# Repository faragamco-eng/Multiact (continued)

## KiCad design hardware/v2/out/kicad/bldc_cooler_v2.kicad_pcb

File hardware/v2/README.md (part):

# شماتیک و چیدمان درایو کولر — نسخه ۲ (برق شهر 220 VAC)

## فایل‌های آماده برای Altium / KiCad

| فایل | توضیح |
|---|---|
| [`out/kicad/`](out/kicad/) | **پروژه کامل KiCad 7**: شماتیک ۸ برگه (+ برگه اصلی)، برد با همه قطعات چیده‌شده، net class ها، قوانین DRC، کتابخانه محلی |
| [`out/bldc_cooler_v2_schematic.pdf`](out/bldc_cooler_v2_schematic.pdf) | شماتیک PDF (۹ صفحه) |
| [`out/bldc_cooler_v2_placement.pdf`](out/bldc_cooler_v2_placement.pdf) | چیدمان برد PDF |
| [`out/bldc_cooler_v2_altium_protel.net`](out/bldc_cooler_v2_altium_protel.net) | نت‌لیست فرمت Protel/Altium (راه جایگزین) |
| [`out/bom.csv`](out/bom.csv) | لیست قطعات (ستون Populate: `yes` یا `OPTION/DNP`) |

### باز کردن در Altium Designer

1. **روش اصلی:** `File → Import Wizard → KiCad Design Files` و انتخاب پوشه `out/kicad`
   (فایل‌های `.kicad_pro`، `.kicad_sch` و `.kicad_pcb`). خروجی: SchDoc برای هر برگه + PcbDoc با چیدمان.
   فرمت KiCad 7 است. Import Wizard در Altium Designer نسخه‌های جدید (22 به بعد) از KiCad 6/7 پشتیبانی می‌کند.
   **من Altium نداشتم و import را خودم تست نکرده‌ام.** پروژه با خود KiCad 7.0.11 بارگذاری و بررسی شده است.
2. **روش جایگزین:** یک PcbDoc خالی، سپس `Design → Import Changes` از روی `bldc_cooler_v2_altium_protel.net`.
   فوت‌پرینت‌ها با همان نام‌های کتابخانه KiCad هستند و باید در کتابخانه Altium شما وجود داشته باشند.

### بررسی‌هایی که روی همین فایل‌ها انجام شد (`./build.sh`)

| بررسی | نتیجه |
|---|---|
| سمبل‌ها، نام پین‌ها، پدهای footprint، عملکرد پین‌های MCU (کتابخانه KiCad 7.0.11 + داده ST) | **0 خطا** (289 قطعه، 199 نت) |
| KiCad نت‌لیست را **از روی شماتیک رسم‌شده** خروجی گرفت و با طراحی مقایسه شد | **0 اختلاف** (172 نت) |
| نت تک‌تک پدهای برد در برابر طراحی | **0 اختلاف** |
| DRC خود KiCad (فاصله‌ها، هم‌پوشانی، لبه برد، سوراخ‌ها) | **0 خطای مسدودکننده**؛ باقی‌مانده: 499 اتصال مسیرکشی‌نشده (مسیرکشی هنوز انجام نشده) و تداخل‌های ظاهری silkscreen |

### چیدمان برد (250 × 180 mm، دولایه)

| ناحیه | محتوا |
|---|---|
| چپ | ورودی AC: ترمینال، فیوز، وریستورها، GDT، چوک CM، خازن‌های X/Y، رله اصلی K1 و پیش‌شارژ K2 |
| وسط چپ | PFC: چوک 470 µH در بالا، کنترلر و قطعات کوچک؛ **دو خازن نو 470 µF/450 V موازی** در یک ردیف پایین‌تر؛ **محل ماژول باتری (DNP)** کنار باس |
| وسط راست | بالا: تغذیه کمکی (VIPer26، پیش‌رگولاتور) |
| پایین (بالای ردیف هیت‌سینک) | **اینورتر گسسته**: سه درایور IRS2186 در سوکت، هر کدام درست بالای دو MOSFET همان فاز، بوت‌استرپ، مقاومت‌های گیت، سه شنت، خازن‌های فیلم |
| راست بالا | **ناحیه SELV** پشت شیار فرز 2 mm (L شکل، زیر T1 و ISO7762): PHY پنل، رگولاتورهای باس پنل، **ترمینال پنل دوسیمه**، RS-485 (DNP) |
| راست پایین | MCU، رله‌های پمپ و تخلیه، ترمینال پمپ/تخلیه 220 V، ترمینال موتور |
| لبه پایین | **ردیف هیت‌سینک**: پل، MOSFET پیش‌رگولاتور، MOSFET PFC، دیود SiC و **شش MOSFET اینورتر TO-247** (عمودی، tab به سمت لبه، با پد عایق و پیچ M3 — قابل تعویض تکی) |

**قوانین برد (در پروژه):** net class `HV_mains` (59 نت برق شهر/باس): فاصله 1.5 mm، ترک 1.5 mm.
`Power_GND`: ترک 2 mm. فاصله داخلی پایه‌های درایورها/MOSFETها/VIPer/رله‌ها با قوانین مخصوص همان قطعه مجاز شده است.
**مرز SELV:** هیچ مسی در 4 mm اطراف شیار نباشد (به‌جز پدهای T1 و U7). خط و یادداشت آن روی لایه Dwgs.User است.

### گزینه‌ها و تجهیزات پایه

* **ماژول باتری (مرحله بعد):** U11 (RS-485)، J8، R99، JP1، C60، F4، J9 روی برد جا دارند ولی **مونتاژ نمی‌شوند** (DNP).
  برای نسخه باتری فقط همین‌ها نصب می‌شوند.
* **پنل:** ترمینال دوسیمه J7 (SELV) و مدار باس پنل کامل روی برد است. طراحی خود پنل در مرحله بعد.
* **تجهیزات پایه از حالا:** 4 سوراخ M3 بدون آبکاری (بدون مسیر خزشی)، 3 فیدوشیال برای مونتاژ ماشینی، 10 نقطه تست
  (+15V، +3V3، GND، درایو گیت PFC، جریان فاز U، UART، +3V3S، GND_S، باس پنل)، کانکتور SWD سمت داغ و سمت SELV،
  LED ولتاژ بالا و LED وضعیت در هر دو سمت.

### کار باقی‌مانده روی برد (دستی)

مسیرکشی انجام نشده است. ترتیب پیشنهادی:
1. حلقه‌های پرجریان: PFC (پل → چوک → MOSFET → دیود → خازن‌ها → شنت → پل) کوتاه و پهن.
2. هر فاز: درین MOSFET بالا ← خازن فیلم همان فاز (C35/C40/C36) ← شنت، حلقه کوچک. درایور با مسیر گیت و برگشت کوتاه (VS مستقیم به سورس MOSFET بالا).
3. شنت‌ها با اتصال Kelvin و ستاره زمین (NT1).
4. سپس سیگنال‌ها. آخر کار polygon زمین در دو سمت (جدا: `GND/PGND` و `GND_S`).

---

## جزئیات طراحی مدار (نسخه ۲)

> نسخه ۱ (`hardware/netlist.md`) برای six-step و تک‌شنت بود و **جایگزین شده است**.

## چطور ساخته و بررسی شده

شماتیک به‌صورت **کد** در [`schematic.py`](schematic.py) تعریف شده است (هر قطعه، هر پین، هر نت). اسکریپت
[`check_and_build.py`](check_and_build.py) آن را با منابع رسمی مقایسه می‌کند و خروجی‌ها را می‌سازد:

| بررسی | منبع |
|---|---|
| هر سمبل وجود دارد، شماره و **نام** هر پین درست است (زنجیره extends حل می‌شود) | کتابخانه رسمی KiCad symbols |
| هر footprint وجود دارد و هر پین وصل‌شده **پد واقعی** دارد | کتابخانه رسمی KiCad footprints |
| پین‌های STM32G431 و STM32C011 با شماره پایه ST یکی است و **هر عملکرد لازم (TIM1، OPAMP، USART، ADC، COMP) واقعاً روی آن پین وجود دارد** | ST `STM32_open_pin_data` |
| نت تک‌اتصالی، تایپوی نت تغذیه، **هیچ قطعه‌ای جز ایزولاتور و ترانس SELV را به سمت برق شهر وصل نکند** | قوانین داخلی |

نتیجه فعلی: **289 قطعه، 199 نت، 0 خطا** (KiCad 7.0.11). سه هشدار باقی‌مانده عمدی هستند: ترانس سفارشی،
پدهای خالی 9/10 ترانس و پین NC رگولاتور. بررسی‌کننده با ۴ خطای عمدی آزمایش شد و هر ۴ را گرفت.

خروجی‌ها در [`out/`](out/):

* `netlist.md` — جدول برگه‌به‌برگه + فهرست نت‌ها
* `bom.csv` — لیست قطعات گروه‌بندی‌شده
* `bldc_cooler_v2.net` — **نت‌لیست KiCad**: در PCB Editor از مسیر *File → Import → Netlist* وارد کنید تا همه
  footprintها و اتصالات (ratsnest) بیایند
* `check_report.txt` — گزارش بررسی
* `calc_v2.md` — محاسبات (PFC، فلای‌بک، سنجش جریان، باس پنل)

اجرای مجدد (کتابخانه‌ها یک بار clone شوند):

```bash
git clone --depth 1 https://gitlab.com/kicad/libraries/kicad-symbols.git
git clone --depth 1 --filter=blob:none --no-checkout https://gitlab.com/kicad/libraries/kicad-footprints.git
git clone --depth 1 --filter=blob:none --sparse https://github.com/STMicroelectronics/STM32_open_pin_data.git
(cd STM32_open_pin_data && git sparse-checkout set --no-cone '/mcu/STM32G431C(6-8-B)Tx.xml' '/mcu/STM32C011F(4-6)Px.xml')
python3 hardware/v2/check_and_build.py --symbols kicad-symbols --footprints kicad-footprints --pindata STM32_open_pin_data
python3 hardware/v2/calc_v2.py
```

## برگه‌ها

| برگه | محتوا | نکات کلیدی |
|---|---|---|
| ۱ ورودی AC | فیوز 10 A، سه MOV نوع **S14K385** + GDT به ارت، X/Y و چوک CM، **K1 رله اصلی** و **K2 پیش‌شارژ با PTC**، یکسوساز تغذیه کمکی **قبل از رله‌ها**، سنجش خط و نول (1:301) | باس فقط وقتی ولتاژ ورودی در محدوده است وصل می‌شود؛ در OV رله‌ها در یک نیم‌سیکل باز می‌شوند |
| ۲ PFC | پل GBU1010، چوک 470 µH، MOSFET 650 V، دیود SiC، شنت 25 mΩ، **NCP1653**، **2×470 µF/450 V نو، 105 °C، موازی** (940 µF: نگه‌داری 49 ms، ریپل 10 V p-p)، بلیدر 3×100k + LED ولتاژ بالا (390 V ⇐ 60 V در ~9 دقیقه) | MCU با Q2 می‌تواند PFC را خاموش کند |
| ۳ تغذیه کمکی | **دیود D29 از باس DC** (نگه‌داری حدود 4 s بعد از قطع برق، کار در حالت باتری) + **پیش‌رگولاتور MOSFET 1500 V** (ورودی فلای‌بک ≤ 395 V حتی در 440 VAC)، VIPer26LN، ترانس EF20 با سه سیم‌پیچ (15 V داغ، 5.5 V و 31 V ایزوله)، باک AP63203 برای 3.3 V داغ، LDO برای 3.3 V ایزوله | پایداری حتی وقتی موتور و PFC قطع‌اند ⇒ پنل همیشه کار می‌کند و آلارم نشان می‌دهد |
| ۴ اینورتر | **گسسته و قابل تعمیر:** 3× **IRS2186** (DIP-8 در سوکت) + 6× **STW24N60DM2** (TO-247، 600 V، دیود بدنه سریع؛ جایگزین IGBT STGW20H60DF)، بوت‌استرپ UF4007 + 10 Ω + 4.7 µF، گیت 10 Ω / 10k، **سه شنت 25 mΩ** در سورس‌های پایین، NTC و **ترموسوئیچ NC 90 °C** هیت‌سینک (به BKIN)، سنجش باس 1:150، NetTie ستاره زمین | ورودی‌ها **فعال-بالا** با pull-down ⇒ `IPM_LIN_ACTIVE_LOW=0`. IRS2186 زمان مرده ندارد ⇒ dead time از TIM1 (≥ 1 µs). اتصال کوتاه: OPAMP → COMP1/2/4 → BKIN2 (داخلی) |
| ۵ MCU | STM32G431CBT6: TIM1 شش PWM، OPAMP1/2/3 و COMP1/2/4 برای سه فاز، ADC برای باس/خط/نول/دما، USART1 به ایزولاتور، ۴ رله، SWD | همه عملکردها با داده ST تأیید شد |
| ۶ رله‌ها | K3 **پمپ** و K4 **تخلیه** (220 VAC)، فیوز 2 A، درایور MOSFET + دیود هرزگرد، اسنابر RC اختیاری | پمپ و تخلیه از **بعد از K1** تغذیه می‌شوند ⇒ در اضافه‌ولتاژ هم قطع می‌شوند |
| ۷ سمت ایزوله | **ISO7762DW (ایزولاسیون تقویت‌شده، SOIC-16 پهن)**، **STM32C011** برای باس پنل و RS-485، باس پنل دوسیمه (LM317 محدودکننده جریان 150 mA + LM317 تنظیم 24/16 V، سنجش جریان برگشتی)، SP3485 به ماژول باتری (DNP) | باس پنل SELV است و پلاریته در پنل مهم نیست |
| ۸ گزینه باتری (DNP) + مکانیک | فیوز DC 5 A / 500 V، ترمینال باس، سوراخ‌ها، فیدوشیال، نقاط تست | در نسخه برق شهر مونتاژ نمی‌شود |

## تفاوت‌ها با اسناد قبلی (مهم)

1. **طبقه قدرت گسسته به جای IPM** (به درخواست شما برای تعمیرپذیری): هر MOSFET و هر درایور جداگانه تعویض می‌شود.
   **IRF840 مناسب نیست** (جدول «Inverter switch losses» در `out/calc_v2.md`: حدود 145 W تلفات در برابر 23 W،
   به‌خاطر 0.85 Ω و دیود بدنه کند 460 ns؛ و 500 V فقط 1.28 برابر باس 390 V است). خازن‌های قدیمی
   1200 µF/200 V بررسی شدند (سه‌تا سری قابل استفاده بود) ولی **به انتخاب شما خازن نو 2×470 µF/450 V** گذاشته شد:
   بدون مقاومت تعادل، بدون ریسک نشتی خازن کهنه، نگه‌داری 49 ms به جای 21 ms. حالت سه‌تا سری در فریمور به‌صورت
   گزینه (`cap_tol`) باقی است.
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
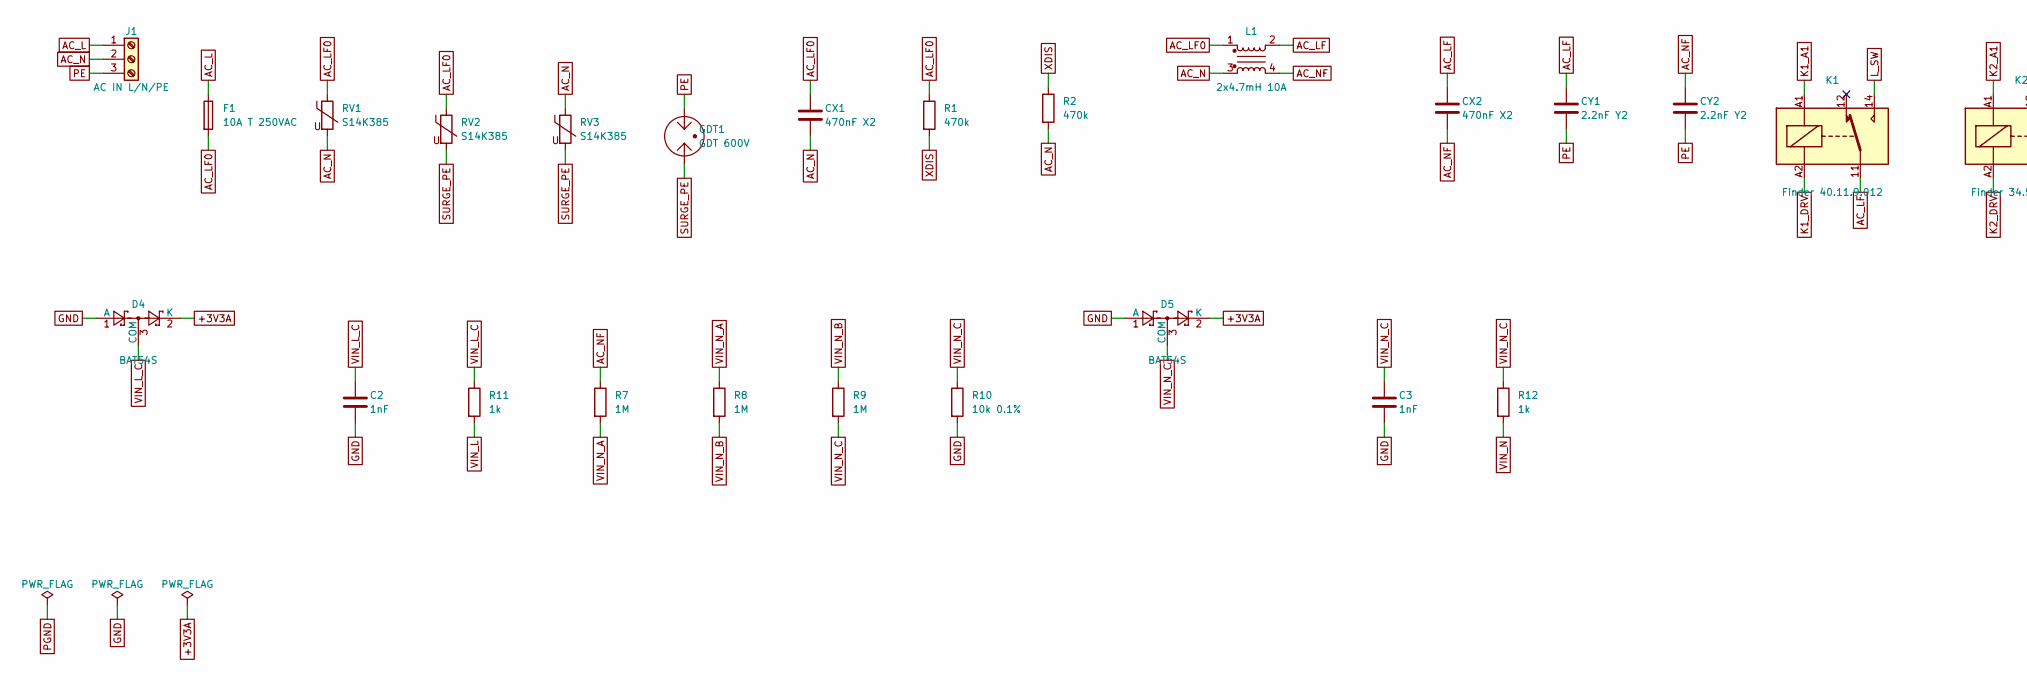
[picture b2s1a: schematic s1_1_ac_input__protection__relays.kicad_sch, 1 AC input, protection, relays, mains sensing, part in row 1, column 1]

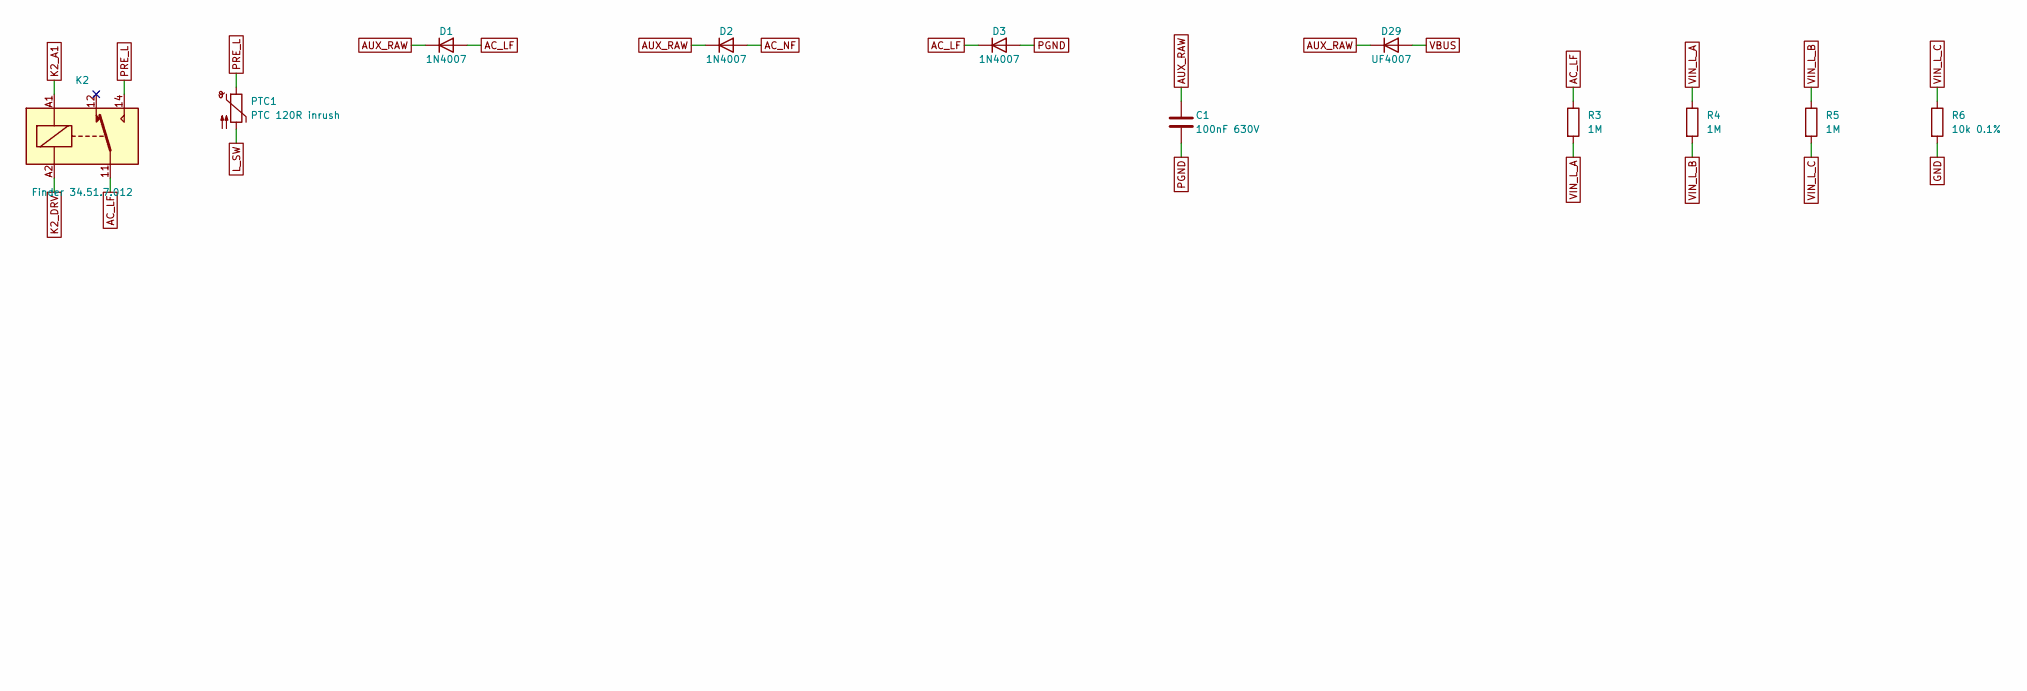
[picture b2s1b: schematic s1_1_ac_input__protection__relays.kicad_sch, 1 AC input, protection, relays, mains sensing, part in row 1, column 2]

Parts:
C1: 100nF 630V; C_Rect_L18.0mm_W6.0mm_P15.00mm_FKS3_FKP3
C2, C3: 1nF; C_0603_1608Metric
CX1: 470nF X2; C_Rect_L18.0mm_W7.0mm_P15.00mm_FKS3_FKP3; MPN X2 310VAC
CX2: 470nF X2; C_Rect_L18.0mm_W7.0mm_P15.00mm_FKS3_FKP3
CY1, CY2: 2.2nF Y2; C_Disc_D11.0mm_W5.0mm_P7.50mm; MPN Y2 300VAC
D1, D2, D3: 1N4007; D_DO-41_SOD81_P10.16mm_Horizontal; MPN 1N4007
D4, D5: BAT54S; SOT-23; MPN BAT54S
D29: UF4007; D_DO-41_SOD81_P10.16mm_Horizontal; MPN UF4007 (1000 V)
F1: 10A T 250VAC; Fuseholder_Cylinder-5x20mm_Bulgin_FX0457_Horizontal_Closed; MPN 5x20 ceramic 10 A time-lag
GDT1: GDT 600V; GDT_Axial_P15.24mm; MPN axial 2-electrode GDT 600 V (e.g. Bourn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
J1: AC IN L/N/PE; TerminalBlock_Phoenix_MKDS-1,5-3-5.08_1x03_P5.08mm_Horizont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; MPN Phoenix MKDS 1,5/3-5,08
K1: Finder 40.11.9.012; Relay_SPDT_Finder_40.11; MPN Finder 40.11.9.012.0000 (10 A, 12 V coi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
K2: Finder 34.51.7.012; Relay_SPDT_Finder_34.51_Vertical; MPN Finder 34.51.7.012.0010
L1: 2x4.7mH 10A; CMC_Toroid_4P_25x15mm; MPN toroidal CM choke 2 x 4.7 mH, >= 10 A (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
PTC1: PTC 120R inrush; C_Disc_D11.0mm_W5.0mm_P7.50mm; MPN inrush PTC rated >= 80 J at 265 VAC (94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
R1, R2: 470k; R_1206_3216Metric
R3, R4, R5, R7, R8, R9: 1M; R_1206_3216Metric
R6, R10: 10k 0.1%; R_0603_1608Metric
R11, R12: 1k; R_0603_1608Metric
RV1: S14K385; RV_Disc_D15.5mm_W11mm_P7.5mm; MPN EPCOS S14K385
RV2, RV3: S14K385; RV_Disc_D15.5mm_W11mm_P7.5mm

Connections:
+3V3A: D4.2 (K), D5.2 (K); also elsewhere on the board
AC_L: F1.1, J1.1
AC_LF: CX2.1, CY1.1, D1.2 (A), D3.1 (K), K1.11, K2.11, L1.2, R3.1
AC_LF0: CX1.1, F1.2, L1.1, R1.1, RV1.1, RV2.1
AC_N: CX1.2, J1.2, L1.3, R2.2, RV1.2, RV3.1
AC_NF: CX2.2, CY2.1, D2.2 (A), L1.4, R7.1; also elsewhere on the board
AUX_RAW: C1.1, D1.1 (K), D2.1 (K), D29.1 (K); also elsewhere on the board
GND: C2.2, C3.2, D4.1 (A), D5.1 (A), R6.2, R10.2; also elsewhere on the board
K1_A1: K1.A1; also elsewhere on the board
K1_DRV: K1.A2; also elsewhere on the board
K2_A1: K2.A1; also elsewhere on the board
K2_DRV: K2.A2; also elsewhere on the board
L_SW: K1.14, PTC1.2; also elsewhere on the board
PE: CY1.2, CY2.2, GDT1.3, J1.3; also elsewhere on the board
PGND: C1.2, D3.2 (A); also elsewhere on the board
PRE_L: K2.14, PTC1.1
SURGE_PE: GDT1.1, RV2.2, RV3.2
VBUS: D29.2 (A); also elsewhere on the board
VIN_L: R11.2; also elsewhere on the board
VIN_L_A: R3.2, R4.1
VIN_L_B: R4.2, R5.1
VIN_L_C: C2.1, D4.3 (COM), R5.2, R6.1, R11.1
VIN_N: R12.2; also elsewhere on the board
VIN_N_A: R7.2, R8.1
VIN_N_B: R8.2, R9.1
VIN_N_C: C3.1, D5.3 (COM), R9.2, R10.1, R12.1
XDIS: R1.2, R2.1

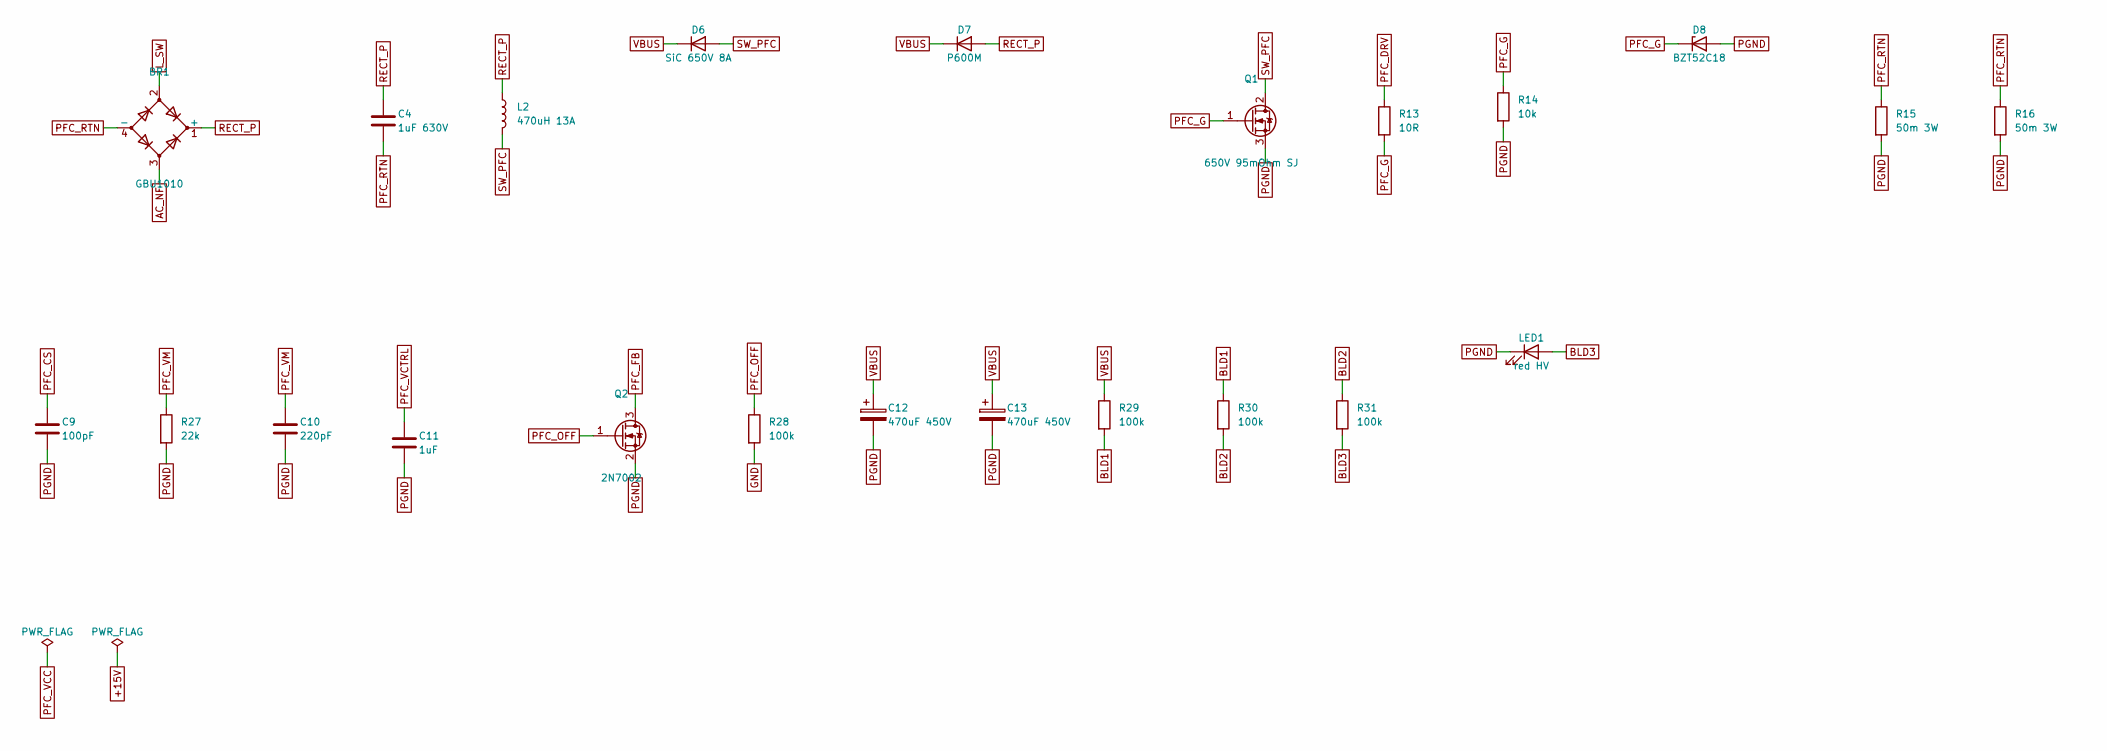
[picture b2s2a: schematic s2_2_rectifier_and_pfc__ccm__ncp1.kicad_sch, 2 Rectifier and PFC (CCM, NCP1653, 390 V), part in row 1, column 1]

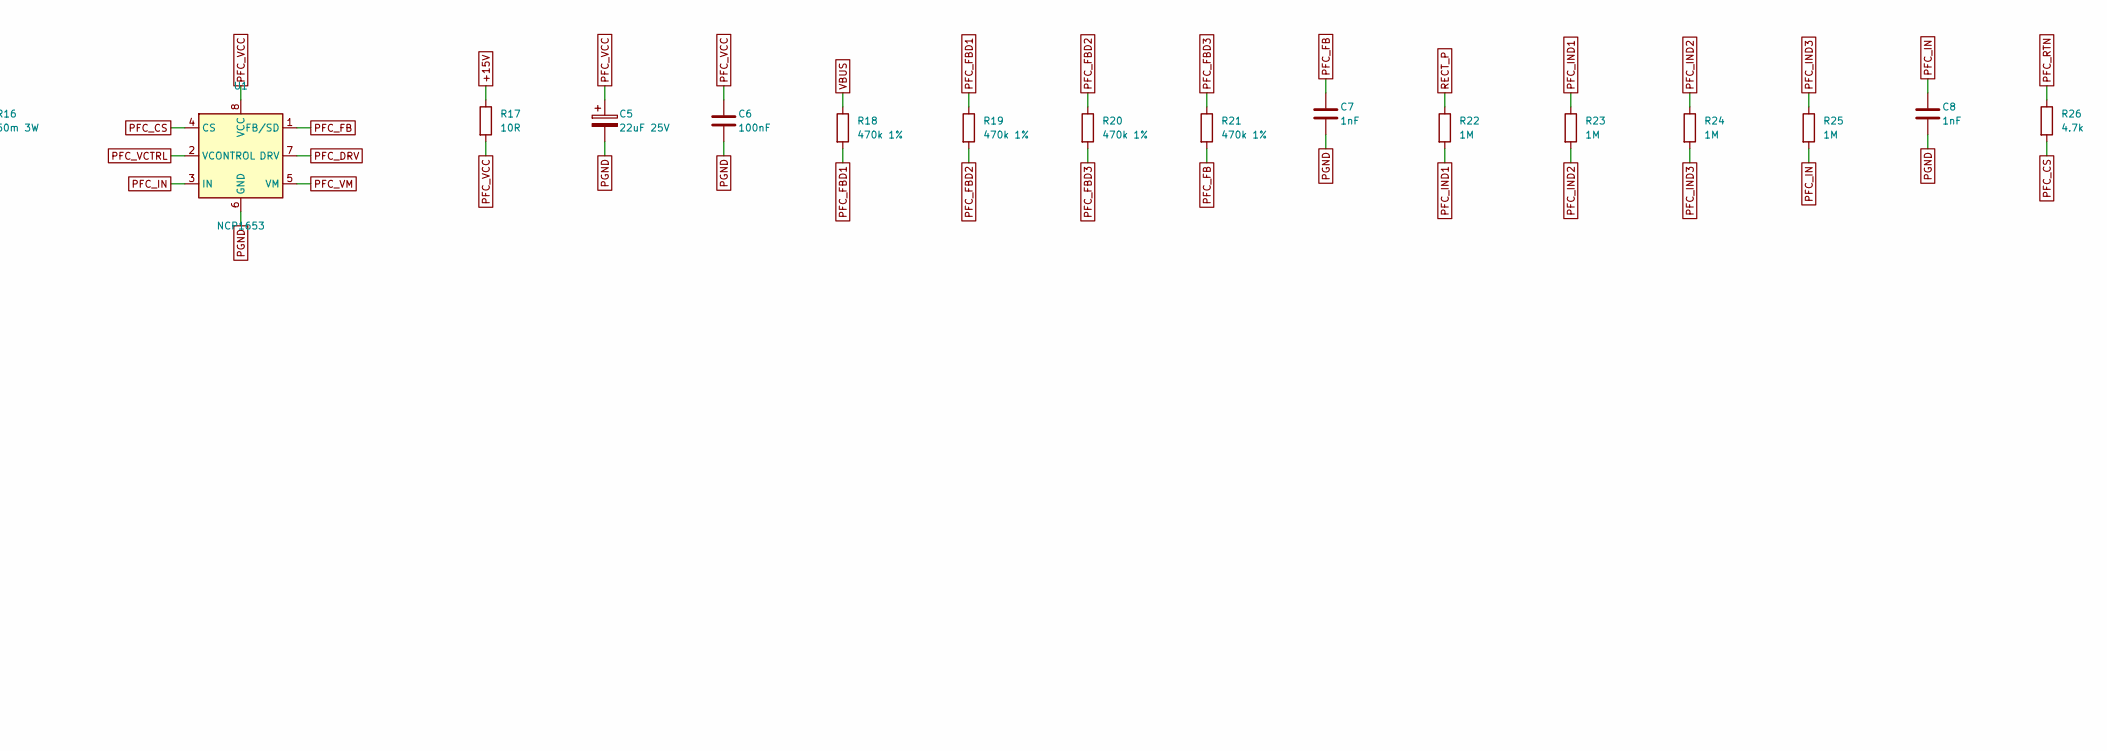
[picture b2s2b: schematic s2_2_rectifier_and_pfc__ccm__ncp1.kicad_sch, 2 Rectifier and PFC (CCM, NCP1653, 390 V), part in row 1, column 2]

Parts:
BR1: GBU1010; Diode_Bridge_Vishay_GBU; MPN GBU1010 (10 A 1000 V) on heatsink
C4: 1uF 630V; C_Rect_L26.5mm_W8.5mm_P22.50mm_MKS4
C5: 22uF 25V; CP_Radial_D8.0mm_P3.50mm
C6: 100nF; C_0603_1608Metric
C7, C8: 1nF; C_0603_1608Metric
C9: 100pF; C_0603_1608Metric
C10: 220pF; C_0603_1608Metric
C11: 1uF; C_0805_2012Metric
C12, C13: 470uF 450V; CP_Radial_D35.0mm_P10.00mm_SnapIn; MPN 470 uF 450 V 105 C >= 5000 h snap-in D3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
D6: SiC 650V 8A; TO-220-2_Vertical; MPN Wolfspeed C3D08065A / Infineon IDH08G65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
D7: P600M; D_DO-201AD_P15.24mm_Horizontal; MPN P600M / 1N5408 inrush bypass
D8: BZT52C18; D_SOD-123; MPN BZT52C18
L2: 470uH 13A; L_Toroid_Vertical_L46.0mm_W19.1mm_P21.80mm_Bourns_5700; MPN toroid ~46 mm OD (e.g. Kool Mu 0077083A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
LED1: red HV; LED_0805_2012Metric; MPN high-efficiency red, 'HIGH VOLTAGE'
Q1: 650V 95mOhm SJ; TO-247-3_Vertical; MPN Infineon IPW65R095C7 / ST STW40N60M6 (h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
Q2: 2N7002; SOT-23; MPN 2N7002
R13, R17: 10R; R_0603_1608Metric
R14: 10k; R_0603_1608Metric
R15, R16: 50m 3W; R_2512_6332Metric
R18, R19, R20, R21: 470k 1%; R_1206_3216Metric
R22, R23, R24, R25: 1M; R_1206_3216Metric
R26: 4.7k; R_0603_1608Metric
R27: 22k; R_0603_1608Metric
R28: 100k; R_0603_1608Metric
R29, R30, R31: 100k; R_1206_3216Metric
U1: NCP1653; SOIC-8_3.9x4.9mm_P1.27mm; MPN onsemi NCP1653ADR2G (67 kHz)

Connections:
+15V: R17.1; also elsewhere on the board
AC_NF: BR1.3; also elsewhere on the board
BLD1: R29.2, R30.1
BLD2: R30.2, R31.1
BLD3: LED1.2 (A), R31.2
GND: R28.2; also elsewhere on the board
L_SW: BR1.2; also elsewhere on the board
PFC_CS: C9.1, R26.2, U1.4 (CS)
PFC_DRV: R13.1, U1.7 (DRV); also elsewhere on the board
PFC_FB: C7.1, Q2.3 (D), R21.2, U1.1 (FB/SD)
PFC_FBD1: R18.2, R19.1
PFC_FBD2: R19.2, R20.1
PFC_FBD3: R20.2, R21.1
PFC_G: D8.1 (K), Q1.1 (G), R13.2, R14.1
PFC_IN: C8.1, R25.2, U1.3 (IN)
PFC_IND1: R22.2, R23.1
PFC_IND2: R23.2, R24.1
PFC_IND3: R24.2, R25.1
PFC_OFF: Q2.1 (G), R28.1; also elsewhere on the board
PFC_RTN: BR1.4 (-), C4.2, R15.1, R16.1, R26.1
PFC_VCC: C5.1, C6.1, R17.2, U1.8 (VCC)
PFC_VCTRL: C11.1, U1.2 (VCONTROL)
PFC_VM: C10.1, R27.1, U1.5 (VM)
PGND: C5.2, C6.2, C7.2, C8.2, C9.2, C10.2, C11.2, C12.2, C13.2, D8.2 (A), LED1.1 (K), Q1.3 (S), Q2.2 (S), R14.2, R15.2, R16.2, R27.2, U1.6 (GND); also elsewhere on the board
RECT_P: BR1.1 (+), C4.1, D7.2 (A), L2.1, R22.1
SW_PFC: D6.2 (A), L2.2, Q1.2 (D)
VBUS: C12.1, C13.1, D6.1 (K), D7.1 (K), R18.1, R29.1; also elsewhere on the board

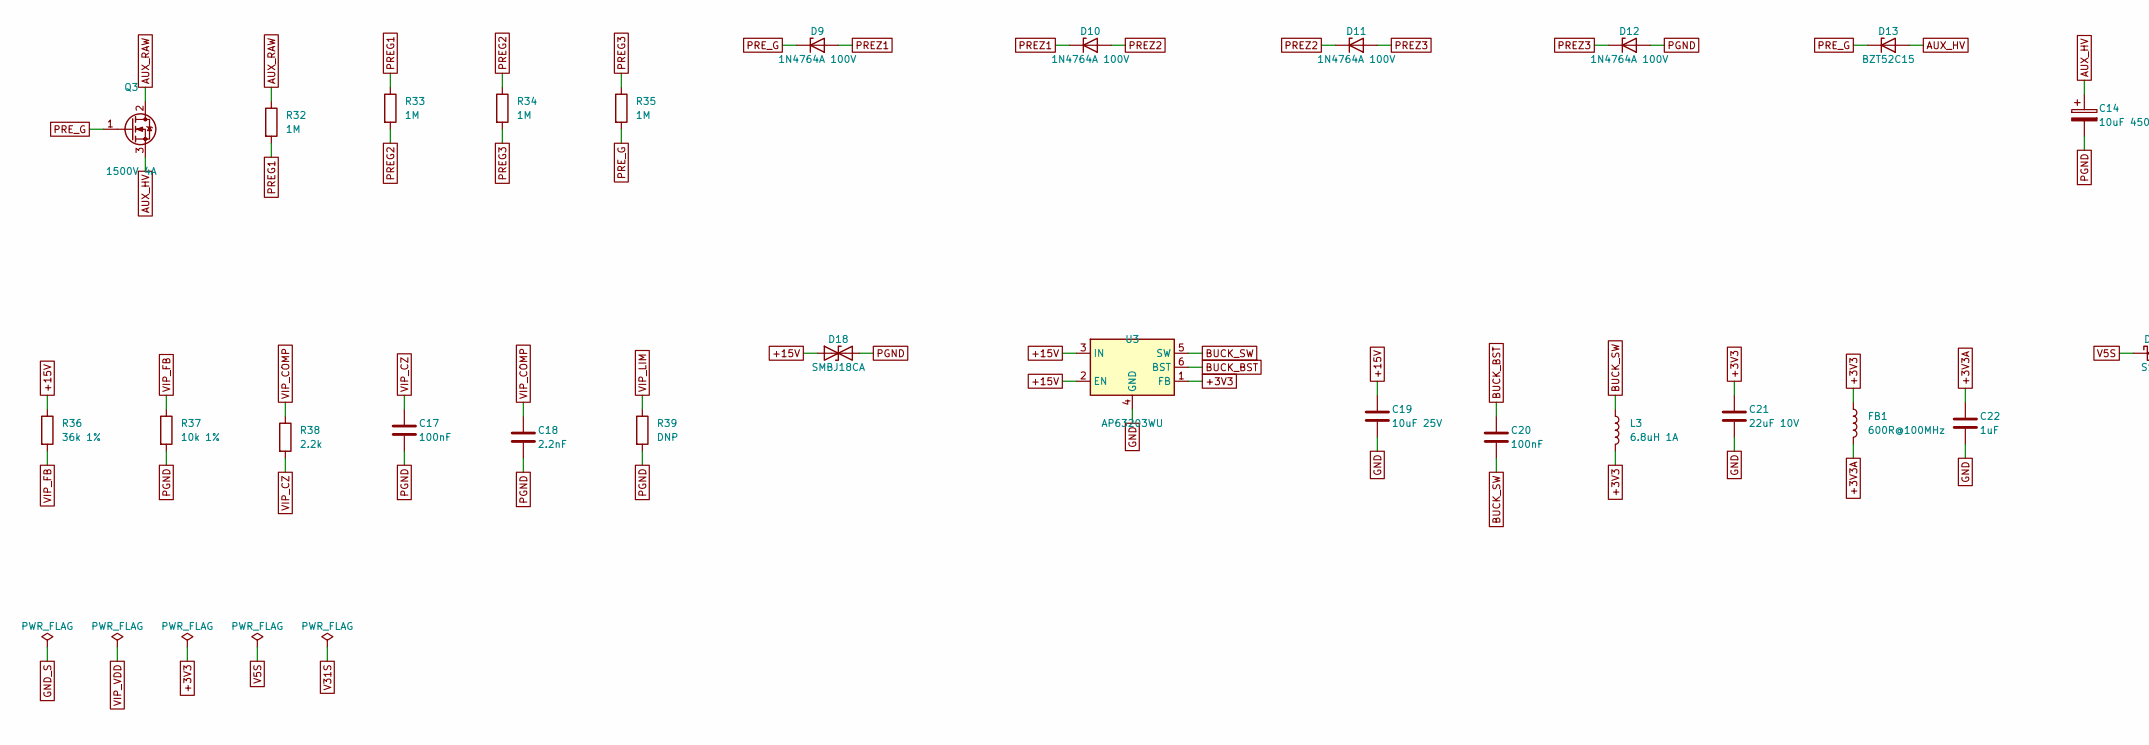
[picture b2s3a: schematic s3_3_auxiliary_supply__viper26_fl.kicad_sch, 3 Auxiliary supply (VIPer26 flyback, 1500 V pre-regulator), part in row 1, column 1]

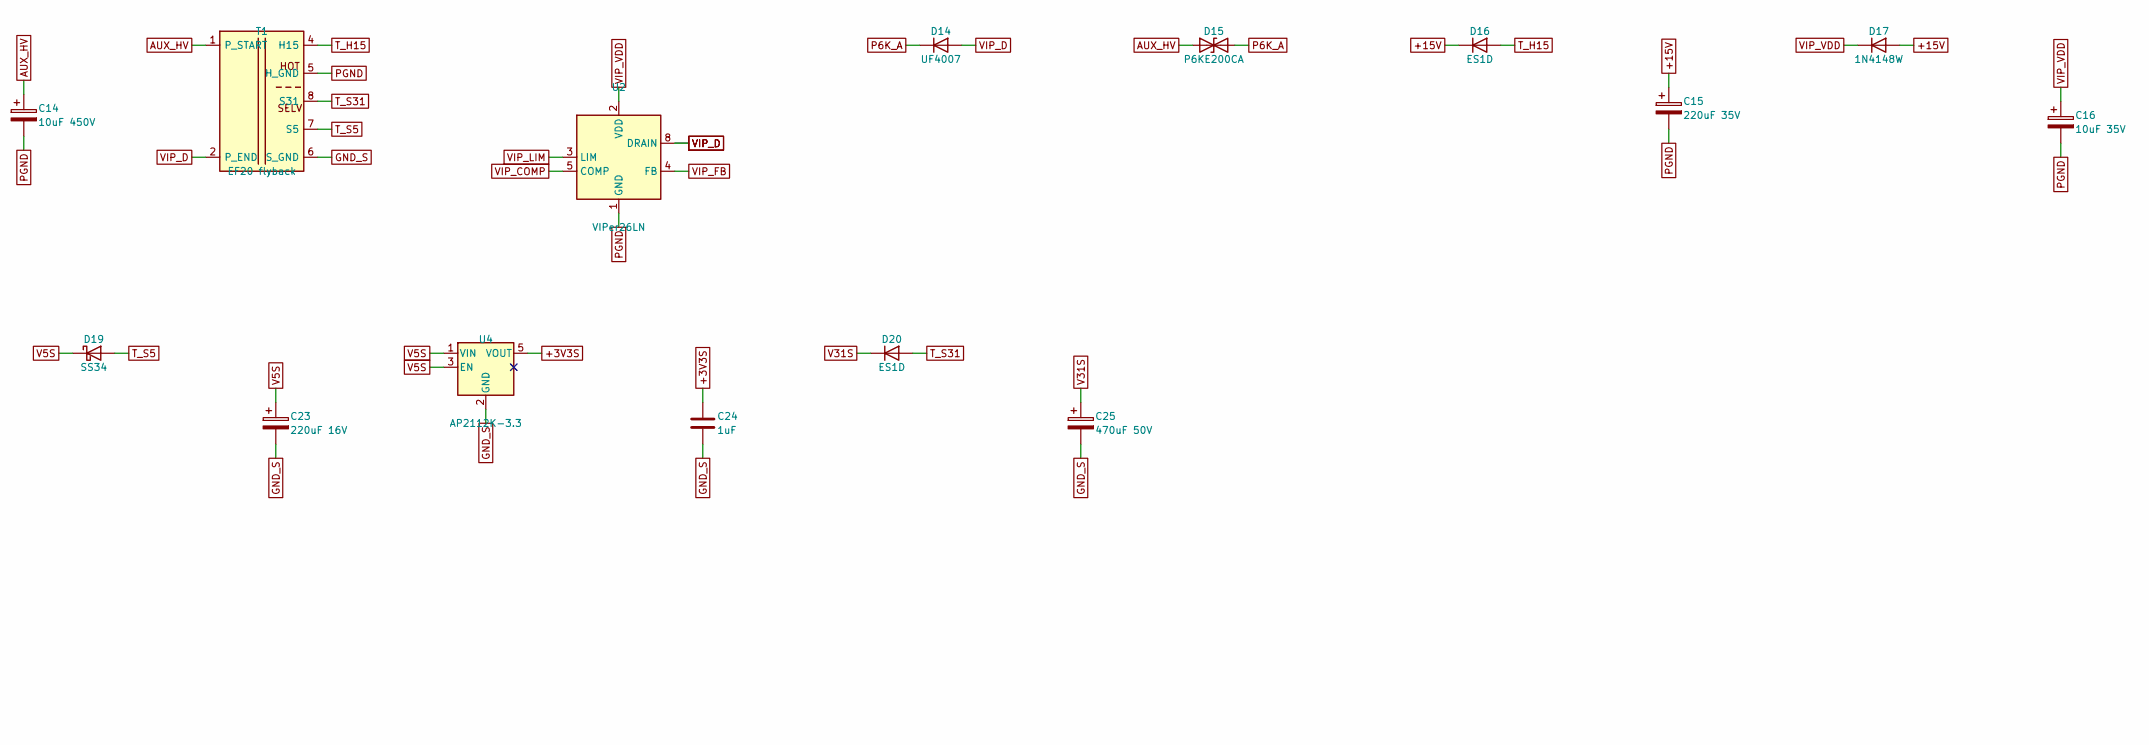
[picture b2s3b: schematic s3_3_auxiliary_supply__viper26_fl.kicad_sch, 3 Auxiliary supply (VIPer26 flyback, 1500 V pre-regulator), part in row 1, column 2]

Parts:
C14: 10uF 450V; CP_Radial_D10.0mm_P5.00mm
C15: 220uF 35V; CP_Radial_D8.0mm_P3.50mm
C16: 10uF 35V; CP_Radial_D8.0mm_P3.50mm
C17, C20: 100nF; C_0603_1608Metric
C18: 2.2nF; C_0603_1608Metric
C19: 10uF 25V; C_1206_3216Metric
C21: 22uF 10V; C_1206_3216Metric
C22, C24: 1uF; C_0603_1608Metric
C23: 220uF 16V; CP_Radial_D8.0mm_P3.50mm
C25: 470uF 50V; CP_Radial_D10.0mm_P5.00mm
D9, D10, D11, D12: 1N4764A 100V; D_DO-41_SOD81_P10.16mm_Horizontal; MPN 1N4764A
D13: BZT52C15; D_SOD-123; MPN BZT52C15
D14: UF4007; D_DO-41_SOD81_P10.16mm_Horizontal; MPN UF4007
D15: P6KE200CA; D_DO-41_SOD81_P10.16mm_Horizontal; MPN P6KE200CA (bidirectional, 200 V clamp)
D16, D20: ES1D; D_SMA; MPN ES1D
D17: 1N4148W; D_SOD-123; MPN 1N4148W
D18: SMBJ18CA; D_SMB; MPN SMBJ18CA
D19: SS34; D_SMA; MPN SS34
FB1: 600R@100MHz; L_0603_1608Metric; MPN ferrite bead
L3: 6.8uH 1A; L_Bourns_SRN6045TA; MPN Bourns SRN6045TA-6R8M
Q3: 1500V 4A; TO-247-3_Vertical; MPN ST STW4N150 (on main heatsink, insulate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
R32, R33, R34, R35: 1M; R_1206_3216Metric
R36: 36k 1%; R_0603_1608Metric
R37: 10k 1%; R_0603_1608Metric
R38: 2.2k; R_0603_1608Metric
R39: DNP; R_0603_1608Metric
T1: EF20 flyback; Transformer_Myrra_EF20_7408x; MPN custom, see calc/transformer spec
U2: VIPer26LN; DIP-8-N6_W7.62mm; MPN ST VIPer26LN (60 kHz)
U3: AP63203WU; TSOT-23-6; MPN Diodes AP63203WU (fixed 3.3 V)
U4: AP2112K-3.3; SOT-23-5; MPN Diodes AP2112K-3.3TRG1

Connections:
+3V3: C21.1, FB1.1, L3.2, U3.1 (FB); also elsewhere on the board
+3V3A: C22.1, FB1.2; also elsewhere on the board
+3V3S: C24.1, U4.5 (VOUT); also elsewhere on the board
+15V: C15.1, C19.1, D16.1 (K), D17.2 (A), D18.1 (A1), R36.1, U3.2 (EN), U3.3 (IN); also elsewhere on the board
AUX_HV: C14.1, D13.2 (A), D15.1 (A1), Q3.3 (S), T1.1 (P_START)
AUX_RAW: Q3.2 (D), R32.1; also elsewhere on the board
BUCK_BST: C20.1, U3.6 (BST)
BUCK_SW: C20.2, L3.1, U3.5 (SW)
GND: C19.2, C21.2, C22.2, U3.4 (GND); also elsewhere on the board
GND_S: C23.2, C24.2, C25.2, T1.6 (S_GND), U4.2 (GND); also elsewhere on the board
P6K_A: D14.1 (K), D15.2 (A2)
PGND: C14.2, C15.2, C16.2, C17.2, C18.2, D12.2 (A), D18.2 (A2), R37.2, R39.2, T1.5 (H_GND), U2.1 (GND); also elsewhere on the board
PREG1: R32.2, R33.1
PREG2: R33.2, R34.1
PREG3: R34.2, R35.1
PREZ1: D9.2 (A), D10.1 (K)
PREZ2: D10.2 (A), D11.1 (K)
PREZ3: D11.2 (A), D12.1 (K)
PRE_G: D9.1 (K), D13.1 (K), Q3.1 (G), R35.2
T_H15: D16.2 (A), T1.4 (H15)
T_S5: D19.2 (A), T1.7 (S5)
T_S31: D20.2 (A), T1.8 (S31)
V5S: C23.1, D19.1 (K), U4.1 (VIN), U4.3 (EN)
V31S: C25.1, D20.1 (K); also elsewhere on the board
VIP_COMP: C18.1, R38.1, U2.5 (COMP)
VIP_CZ: C17.1, R38.2
VIP_D: D14.2 (A), T1.2 (P_END), U2.7 (DRAIN), U2.8 (DRAIN)
VIP_FB: R36.2, R37.1, U2.4 (FB)
VIP_LIM: R39.1, U2.3 (LIM)
VIP_VDD: C16.1, D17.1 (K), U2.2 (VDD)

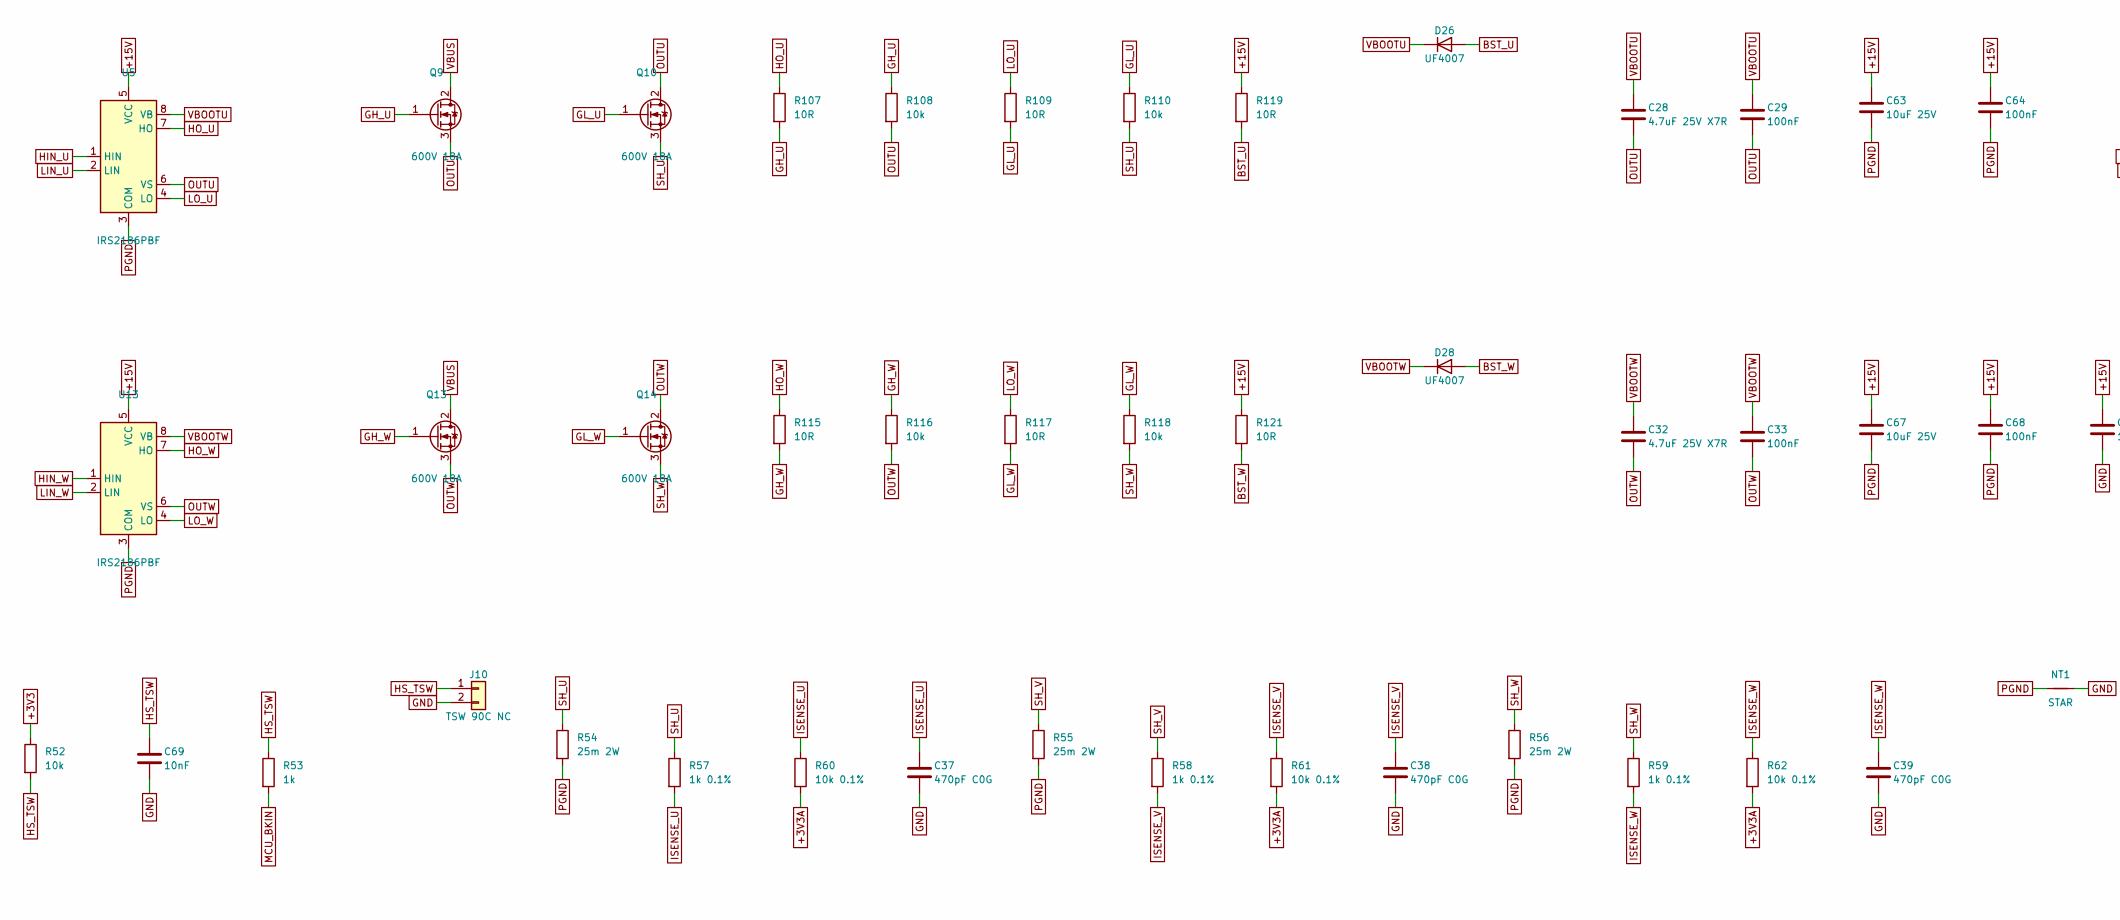
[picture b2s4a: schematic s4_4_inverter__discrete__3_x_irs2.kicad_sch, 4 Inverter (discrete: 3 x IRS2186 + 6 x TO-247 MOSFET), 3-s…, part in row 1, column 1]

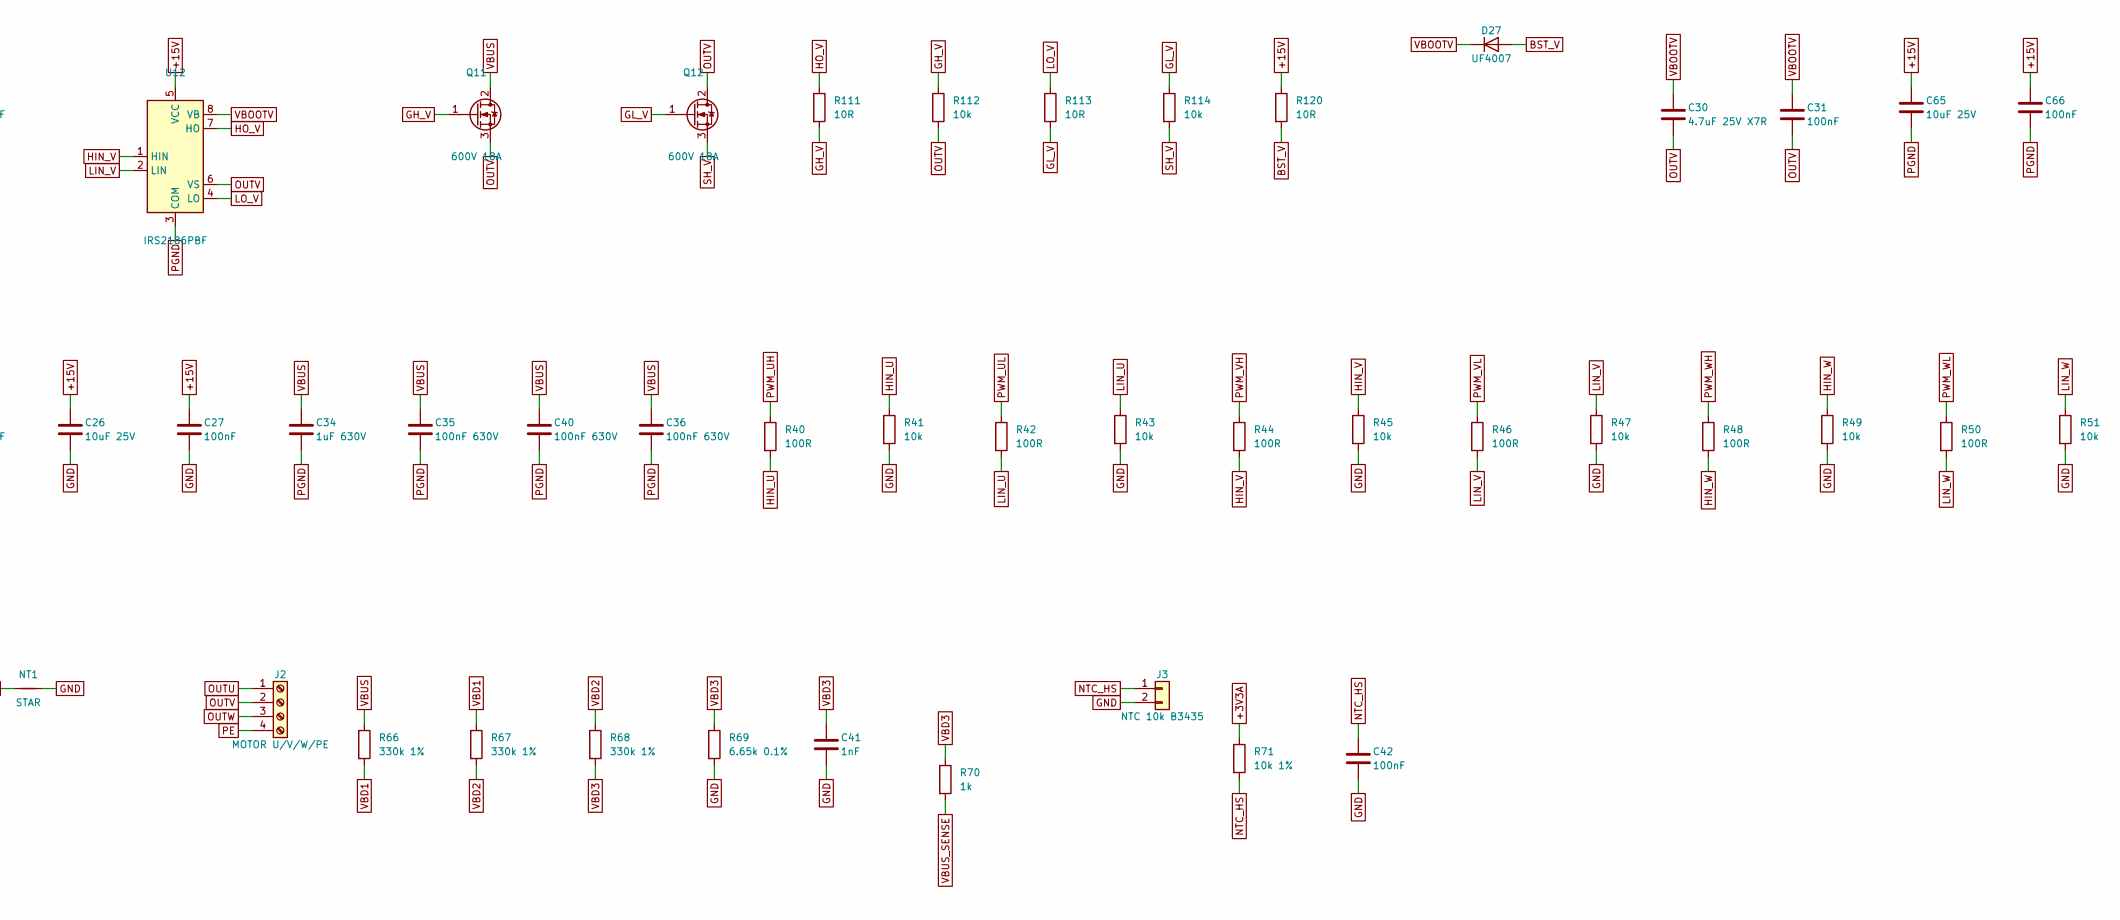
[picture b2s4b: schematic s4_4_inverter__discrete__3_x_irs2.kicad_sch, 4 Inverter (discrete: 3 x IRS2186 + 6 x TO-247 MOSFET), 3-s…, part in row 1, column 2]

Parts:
C26, C63, C65, C67: 10uF 25V; C_1206_3216Metric
C27, C29, C31, C33, C42, C64, C66, C68: 100nF; C_0603_1608Metric
C28, C30, C32: 4.7uF 25V X7R; C_1206_3216Metric
C34: 1uF 630V; C_Rect_L26.5mm_W8.5mm_P22.50mm_MKS4
C35, C36, C40: 100nF 630V; C_Rect_L18.0mm_W6.0mm_P15.00mm_FKS3_FKP3
C37, C38, C39: 470pF C0G; C_0603_1608Metric
C41: 1nF; C_0603_1608Metric
C69: 10nF; C_0603_1608Metric
D26, D27, D28: UF4007; D_DO-41_SOD81_P10.16mm_Horizontal; MPN UF4007 (1000 V, 75 ns)
J2: MOTOR U/V/W/PE; TerminalBlock_Phoenix_MKDS-1,5-4-5.08_1x04_P5.08mm_Horizont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
J3: NTC 10k B3435; PinHeader_1x02_P2.54mm_Vertical; MPN screw-lug NTC 10k B3435 on heatsink
J10: TSW 90C NC; PinHeader_1x02_P2.54mm_Vertical; MPN KSD301 90 C normally closed, on heatsink
NT1: STAR; NetTie-2_SMD_Pad0.5mm
Q9, Q10, Q11, Q12, Q13, Q14: 600V 18A; TO-247-3_Vertical; MPN ST STW24N60DM2 (fast body diode) / alt.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
R40, R42, R44, R46, R48, R50: 100R; R_0603_1608Metric
R41, R43, R45, R47, R49, R51, R52, R108, R110, R112, R114, R116, R118: 10k; R_0603_1608Metric
R53, R70: 1k; R_0603_1608Metric
R54, R55, R56: 25m 2W; R_2512_6332Metric
R57, R58, R59: 1k 0.1%; R_0603_1608Metric
R60, R61, R62: 10k 0.1%; R_0603_1608Metric
R66, R67, R68: 330k 1%; R_1206_3216Metric
R69: 6.65k 0.1%; R_0603_1608Metric
R71: 10k 1%; R_0603_1608Metric
R107, R109, R111, R113, R115, R117, R119, R120, R121: 10R; R_1206_3216Metric
U5, U12, U13: IRS2186PBF; DIP-8_W7.62mm_Socket; MPN Infineon IRS2186PBF (DIP-8 in socket)

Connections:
+3V3: R52.1; also elsewhere on the board
+3V3A: R60.2, R61.2, R62.2, R71.1; also elsewhere on the board
+15V: C26.1, C27.1, C63.1, C64.1, C65.1, C66.1, C67.1, C68.1, R119.1, R120.1, R121.1, U5.5 (VCC), U12.5 (VCC), U13.5 (VCC); also elsewhere on the board
BST_U: D26.2 (A), R119.2
BST_V: D27.2 (A), R120.2
BST_W: D28.2 (A), R121.2
GH_U: Q9.1 (G), R107.2, R108.1
GH_V: Q11.1 (G), R111.2, R112.1
GH_W: Q13.1 (G), R115.2, R116.1
GL_U: Q10.1 (G), R109.2, R110.1
GL_V: Q12.1 (G), R113.2, R114.1
GL_W: Q14.1 (G), R117.2, R118.1
GND: C26.2, C27.2, C37.2, C38.2, C39.2, C41.2, C42.2, C69.2, J3.2, J10.2, NT1.2, R41.2, R43.2, R45.2, R47.2, R49.2, R51.2, R69.2; also elsewhere on the board
HIN_U: R40.2, R41.1, U5.1 (HIN)
HIN_V: R44.2, R45.1, U12.1 (HIN)
HIN_W: R48.2, R49.1, U13.1 (HIN)
HO_U: R107.1, U5.7 (HO)
HO_V: R111.1, U12.7 (HO)
HO_W: R115.1, U13.7 (HO)
HS_TSW: C69.1, J10.1, R52.2, R53.1
ISENSE_U: C37.1, R57.2, R60.1; also elsewhere on the board
ISENSE_V: C38.1, R58.2, R61.1; also elsewhere on the board
ISENSE_W: C39.1, R59.2, R62.1; also elsewhere on the board
LIN_U: R42.2, R43.1, U5.2 (LIN)
LIN_V: R46.2, R47.1, U12.2 (LIN)
LIN_W: R50.2, R51.1, U13.2 (LIN)
LO_U: R109.1, U5.4 (LO)
LO_V: R113.1, U12.4 (LO)
LO_W: R117.1, U13.4 (LO)
MCU_BKIN: R53.2; also elsewhere on the board
NTC_HS: C42.1, J3.1, R71.2; also elsewhere on the board
OUTU: C28.2, C29.2, J2.1, Q9.3 (S), Q10.2 (D), R108.2, U5.6 (VS)
OUTV: C30.2, C31.2, J2.2, Q11.3 (S), Q12.2 (D), R112.2, U12.6 (VS)
OUTW: C32.2, C33.2, J2.3, Q13.3 (S), Q14.2 (D), R116.2, U13.6 (VS)
PE: J2.4; also elsewhere on the board
PGND: C34.2, C35.2, C36.2, C40.2, C63.2, C64.2, C65.2, C66.2, C67.2, C68.2, NT1.1, R54.2, R55.2, R56.2, U5.3 (COM), U12.3 (COM), U13.3 (COM); also elsewhere on the board
PWM_UH: R40.1; also elsewhere on the board
PWM_UL: R42.1; also elsewhere on the board
PWM_VH: R44.1; also elsewhere on the board
PWM_VL: R46.1; also elsewhere on the board
PWM_WH: R48.1; also elsewhere on the board
PWM_WL: R50.1; also elsewhere on the board
SH_U: Q10.3 (S), R54.1, R57.1, R110.2
SH_V: Q12.3 (S), R55.1, R58.1, R114.2
SH_W: Q14.3 (S), R56.1, R59.1, R118.2
VBD1: R66.2, R67.1
VBD2: R67.2, R68.1
VBD3: C41.1, R68.2, R69.1, R70.1
VBOOTU: C28.1, C29.1, D26.1 (K), U5.8 (VB)
VBOOTV: C30.1, C31.1, D27.1 (K), U12.8 (VB)
VBOOTW: C32.1, C33.1, D28.1 (K), U13.8 (VB)
VBUS: C34.1, C35.1, C36.1, C40.1, Q9.2 (D), Q11.2 (D), Q13.2 (D), R66.1; also elsewhere on the board
VBUS_SENSE: R70.2; also elsewhere on the board
